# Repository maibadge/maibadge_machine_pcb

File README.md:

# maibadge-machine-pcb
maimai badge project. PCB badges with maimai themes

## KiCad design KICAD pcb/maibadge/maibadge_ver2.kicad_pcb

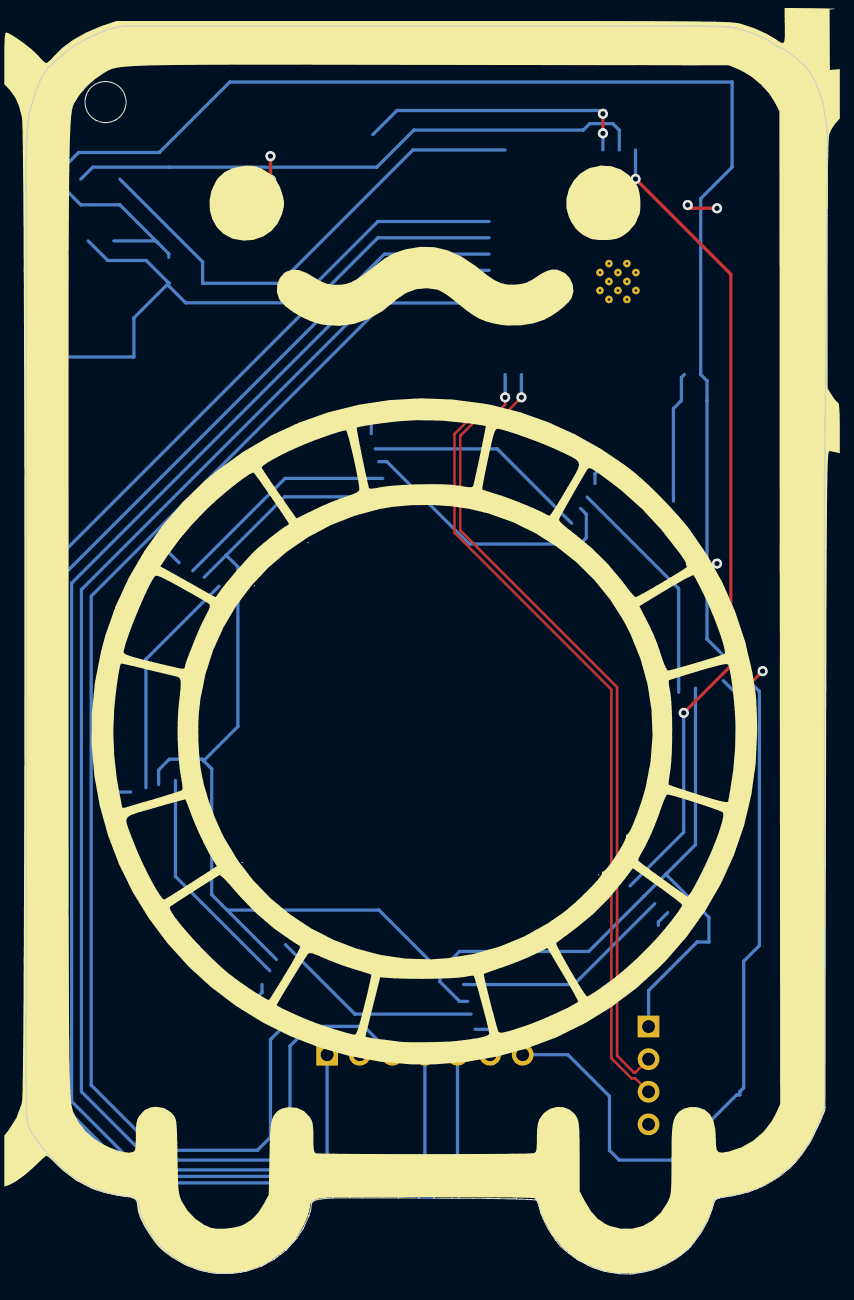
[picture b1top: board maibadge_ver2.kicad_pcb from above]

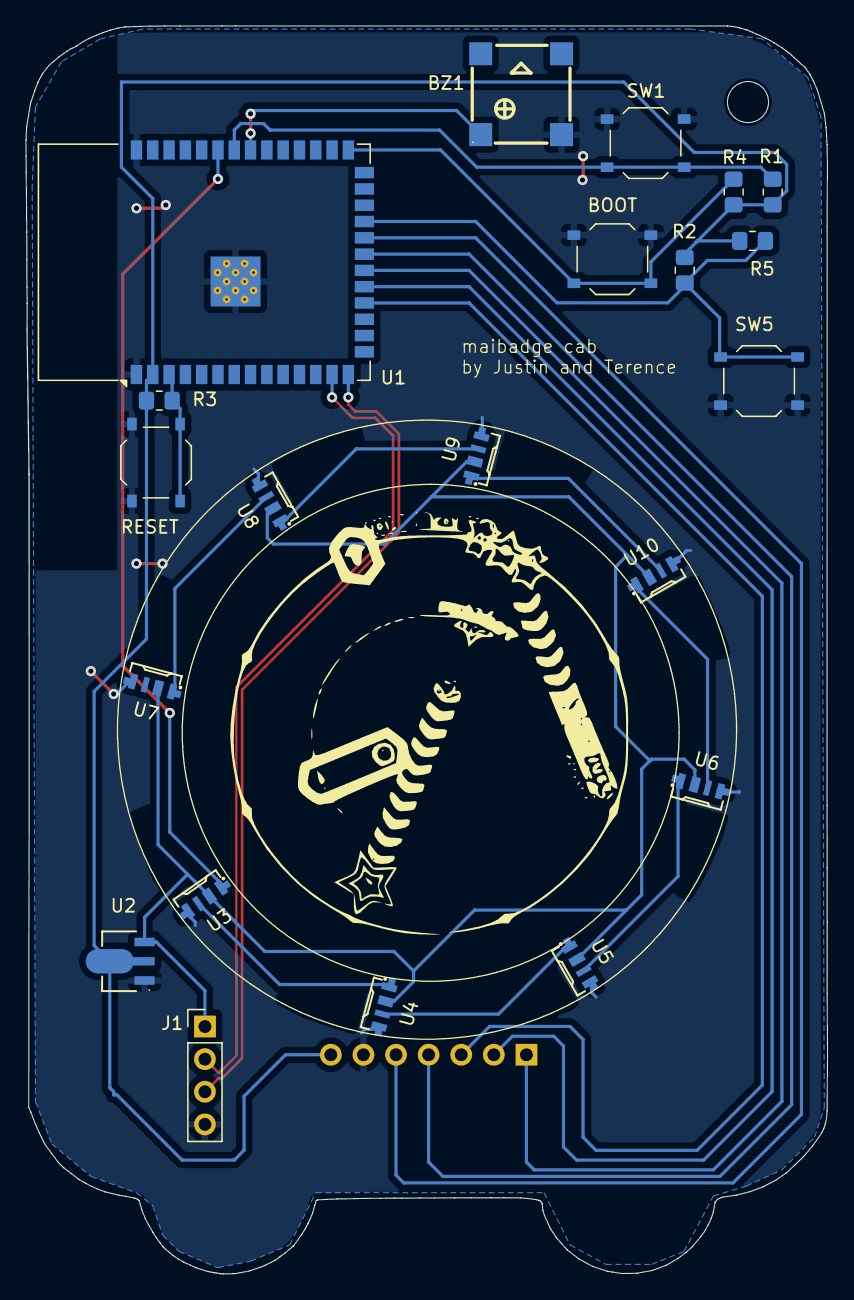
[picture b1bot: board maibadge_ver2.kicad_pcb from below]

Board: 2 copper layers, 62.4 x 97.2 mm, 22 parts (21 on the bottom side), 23 nets.

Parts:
BOOT: SW_Push; SW_Push_1P1T_XKB_TS-1187A
BZ1: Buzzer; BUZ-SMD_4P-L7.5-W7.5-BR
GC9A1: CG9A01; GC9A01
J1: Conn_01x04_Socket; PinHeader_1x04_P2.54mm_Vertical
R1, R2, R3, R4, R5: R; R_0805_2012Metric_Pad1.20x1.40mm_HandSolder
RESET: SW_Push; SW_Push_1P1T_XKB_TS-1187A
SW1, SW5: SW_Push; SW_Push_1P1T_XKB_TS-1187A
U1: ESP32-S3-WROOM-1
U2: AMS1117-3.3; SOT-89-3_L4.5-W2.5-P1.50-LS4.2-BR
U3, U4, U5, U6, U7, U8, U9, U10: SK6812SIDE-A-RVS; LED-SMD_4P-L4.0-W1.6-L

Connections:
+3.3V: GC9A1.7 (VCC), R1.1, R2.1, R3.1, R4.1, R5.1, U1.2 (3V3), U2.2 (VOUT)
+5V: J1.1, U2.3 (VIN), U3.2 (VDD), U4.2 (VDD), U5.2 (VDD), U6.2 (VDD), U7.2 (VDD), U8.2 (VDD), U9.2 (VDD), U10.2 (VDD)
/CHIP_PU: R3.2, RESET.2, U1.3 (EN)
/GPIO0_BOOT: BOOT.2, R4.2, U1.27 (IO0)
/OLED_CS: GC9A1.2 (CS), U1.19 (IO11)
/OLED_DC: GC9A1.3 (DC), U1.18 (IO10)
/OLED_RST: GC9A1.1 (RST), U1.20 (IO12)
/OLED_SCL: GC9A1.5 (SCL), U1.22 (IO14)
/OLED_SDA: GC9A1.4 (SDA), U1.21 (IO13)
/USB_D+: J1.3, U1.14 (IO20)
/USB_D-: J1.2, U1.13 (IO19)
/button 1: R2.2, R5.2, SW5.2, U1.23 (IO21)
/button 2: R1.2, SW1.2, U1.34 (IO41)
/buzzer: BZ1.1 (+), U1.33 (IO40)
/main led DIN: U1.35 (IO42), U3.1 (DIN)
GND: BOOT.1, BZ1.2 (-), GC9A1.6 (GND), J1.4, RESET.1, SW1.1, SW5.1, U1.1 (GND), U1.40 (GND), U1.41 (GND), U2.1 (GND/ADJ), U3.4 (GND), U4.4 (GND), U5.4 (GND), U6.4 (GND), U7.4 (GND), U8.4 (GND), U9.4 (GND), U10.4 (GND)
unnamed: U3.3 (DOUT), U4.1 (DIN)
unnamed: U4.3 (DOUT), U5.1 (DIN)
unnamed: U5.3 (DOUT), U6.1 (DIN)
unnamed: U7.1 (DIN), U8.3 (DOUT)
unnamed: U8.1 (DIN), U9.3 (DOUT)
unnamed: U6.3 (DOUT), U10.1 (DIN)
unnamed: U9.1 (DIN), U10.3 (DOUT)

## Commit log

2025-01-12 README.md
2025-01-12 KICAD
2025-01-12 Create maibadge 12 Jan
2025-01-20 Create a
2025-01-25 feat: submit updated files
2025-01-25 fix: silkscreen invert
2025-01-25 fix: schematic and routing
2025-01-25 chore: organise files
2025-01-25 chore: cleanup
2025-02-04 feat: update pcb image
2025-08-07 feat: firmware + kicad gitignore
2025-08-07 feat: untested code changes to allow for button control
2025-08-19 image stuff
2025-09-22 feat: maibadge cab v2
